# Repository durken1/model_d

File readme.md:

# Model D

## Note: I got this working using a fork of QMK for XWhatsit by deskthority user pandrew. There is probably room for improvement in the PCB - the current version is basically a working prototype, so use this at your own peril. No guarantees :)

40% ortho keyboard using a capacitive pcb and Model F switches.

The ground plate is important to avoid interference and is to be placed beneath the main pcb.

## Case
I have included the STLs (cut to be printable on "normal" sized printers, I used an Ender 3 V2) for my case as well as the step file, so it should be easy to make adjustments to fit your need. 
I used M3 inserts and screws for attaching stuff (all the 4mm round holes).

The PCBs slide into the plate that is then attached to the main case using the mounting bracket. The plate is designed with 0.8 mm PCBs in mind (1.6 mm total for main + ground pcb).

I think most of the assembly is pretty straight forward, so I won't make a guide unless there is demand for one. Feel free to contact me with any questions though.

For my build I used a TH-xwhatsit and a short USB C panel mount extension cable.

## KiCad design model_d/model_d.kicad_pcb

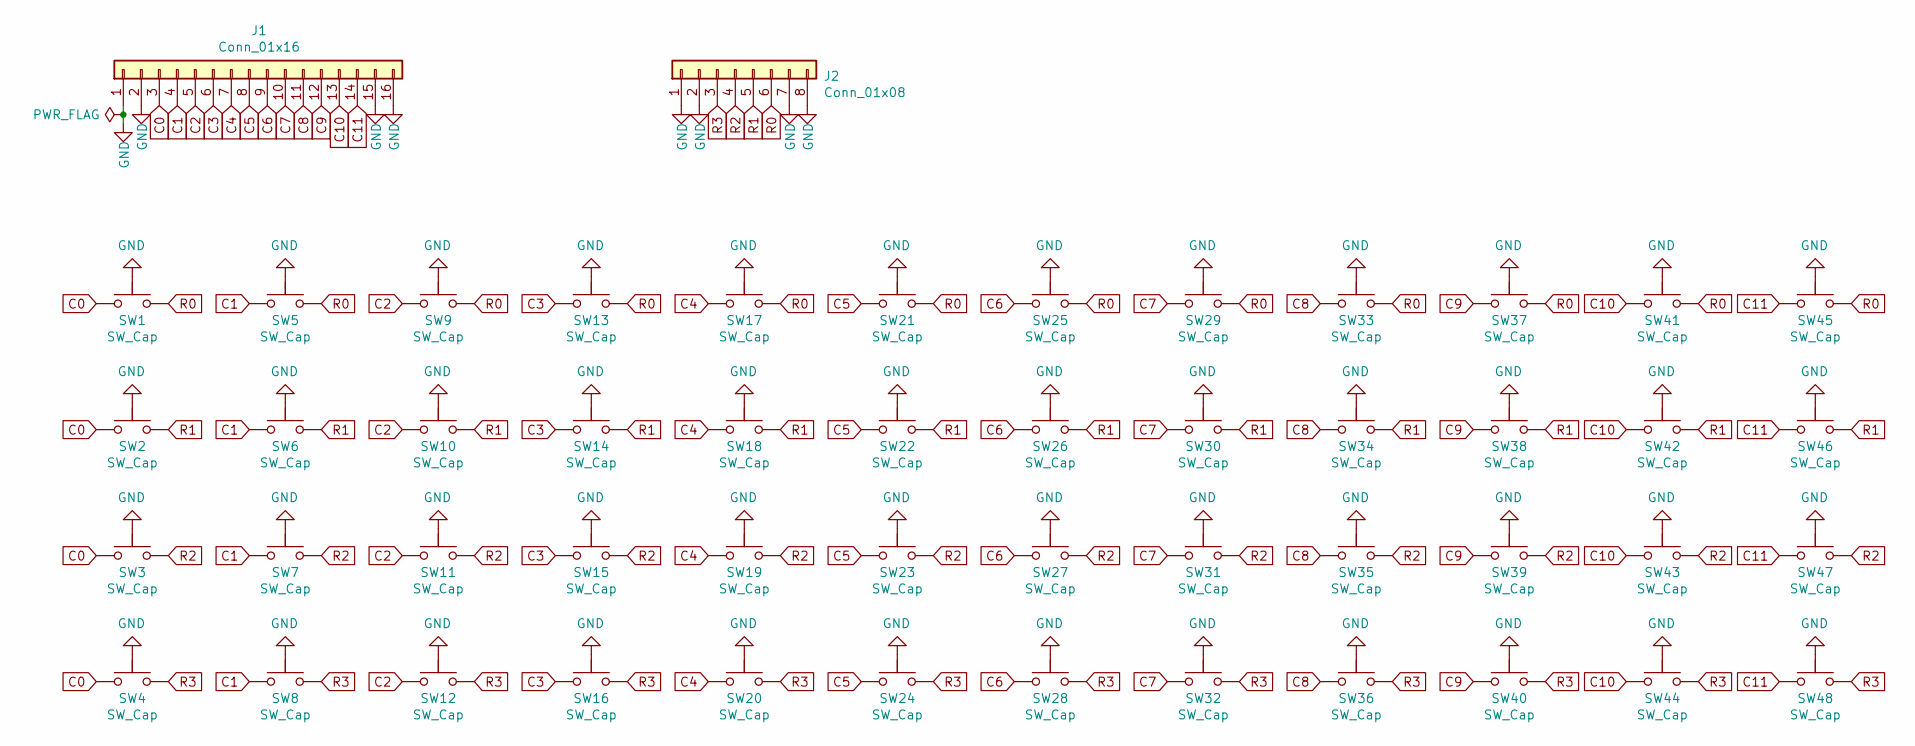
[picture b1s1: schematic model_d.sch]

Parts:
J1: Conn_01x16; PinHeader_1x16_P2.54mm_Vertical
J2: Conn_01x08; PinHeader_1x08_P2.54mm_Vertical
SW1, SW2, SW3, SW4, SW5, SW6, SW7, SW8, SW9, SW10, SW11, SW12, SW13, SW14, SW15, SW16, SW17, SW18, SW19, SW20, SW21, SW22, SW23, SW24, SW25, SW26, SW27, SW28, SW29, SW30, SW31, SW32, SW33, SW34, SW35, SW36, SW37, SW38, SW39, SW40, SW41, SW42, SW43, SW44, SW45, SW46, SW47, SW48: SW_Cap; capswitch2

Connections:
C0: J1.3, SW1.DRIVE, SW2.DRIVE, SW3.DRIVE, SW4.DRIVE; also elsewhere on the board
C1: J1.4, SW5.DRIVE, SW6.DRIVE, SW7.DRIVE, SW8.DRIVE; also elsewhere on the board
C2: J1.5, SW9.DRIVE, SW10.DRIVE, SW11.DRIVE, SW12.DRIVE; also elsewhere on the board
C3: J1.6, SW13.DRIVE, SW14.DRIVE, SW15.DRIVE, SW16.DRIVE; also elsewhere on the board
C4: J1.7, SW17.DRIVE, SW18.DRIVE, SW19.DRIVE, SW20.DRIVE; also elsewhere on the board
C5: J1.8, SW21.DRIVE, SW22.DRIVE, SW23.DRIVE, SW24.DRIVE; also elsewhere on the board
C6: J1.9, SW25.DRIVE, SW26.DRIVE, SW27.DRIVE, SW28.DRIVE; also elsewhere on the board
C7: J1.10, SW29.DRIVE, SW30.DRIVE, SW31.DRIVE, SW32.DRIVE; also elsewhere on the board
C8: J1.11, SW33.DRIVE, SW34.DRIVE, SW35.DRIVE, SW36.DRIVE; also elsewhere on the board
C9: J1.12, SW37.DRIVE, SW38.DRIVE, SW39.DRIVE, SW40.DRIVE; also elsewhere on the board
C10: J1.13, SW41.DRIVE, SW42.DRIVE, SW43.DRIVE, SW44.DRIVE; also elsewhere on the board
C11: J1.14, SW45.DRIVE, SW46.DRIVE, SW47.DRIVE, SW48.DRIVE; also elsewhere on the board
GND: J1.1, J1.2, J1.15, J1.16, J2.1, J2.2, J2.7, J2.8, SW1.GND, SW2.GND, SW3.GND, SW4.GND, SW5.GND, SW6.GND, SW7.GND, SW8.GND, SW9.GND, SW10.GND, SW11.GND, SW12.GND, SW13.GND, SW14.GND, SW15.GND, SW16.GND, SW17.GND, SW18.GND, SW19.GND, SW20.GND, SW21.GND, SW22.GND, SW23.GND, SW24.GND, SW25.GND, SW26.GND, SW27.GND, SW28.GND, SW29.GND, SW30.GND, SW31.GND, SW32.GND, SW33.GND, SW34.GND, SW35.GND, SW36.GND, SW37.GND, SW38.GND, SW39.GND, SW40.GND, SW41.GND, SW42.GND, SW43.GND, SW44.GND, SW45.GND, SW46.GND, SW47.GND, SW48.GND; also elsewhere on the board
R0: J2.6, SW1.SENSE, SW5.SENSE, SW9.SENSE, SW13.SENSE, SW17.SENSE, SW21.SENSE, SW25.SENSE, SW29.SENSE, SW33.SENSE, SW37.SENSE, SW41.SENSE, SW45.SENSE; also elsewhere on the board
R1: J2.5, SW2.SENSE, SW6.SENSE, SW10.SENSE, SW14.SENSE, SW18.SENSE, SW22.SENSE, SW26.SENSE, SW30.SENSE, SW34.SENSE, SW38.SENSE, SW42.SENSE, SW46.SENSE; also elsewhere on the board
R2: J2.4, SW3.SENSE, SW7.SENSE, SW11.SENSE, SW15.SENSE, SW19.SENSE, SW23.SENSE, SW27.SENSE, SW31.SENSE, SW35.SENSE, SW39.SENSE, SW43.SENSE, SW47.SENSE; also elsewhere on the board
R3: J2.3, SW4.SENSE, SW8.SENSE, SW12.SENSE, SW16.SENSE, SW20.SENSE, SW24.SENSE, SW28.SENSE, SW32.SENSE, SW36.SENSE, SW40.SENSE, SW44.SENSE, SW48.SENSE; also elsewhere on the board

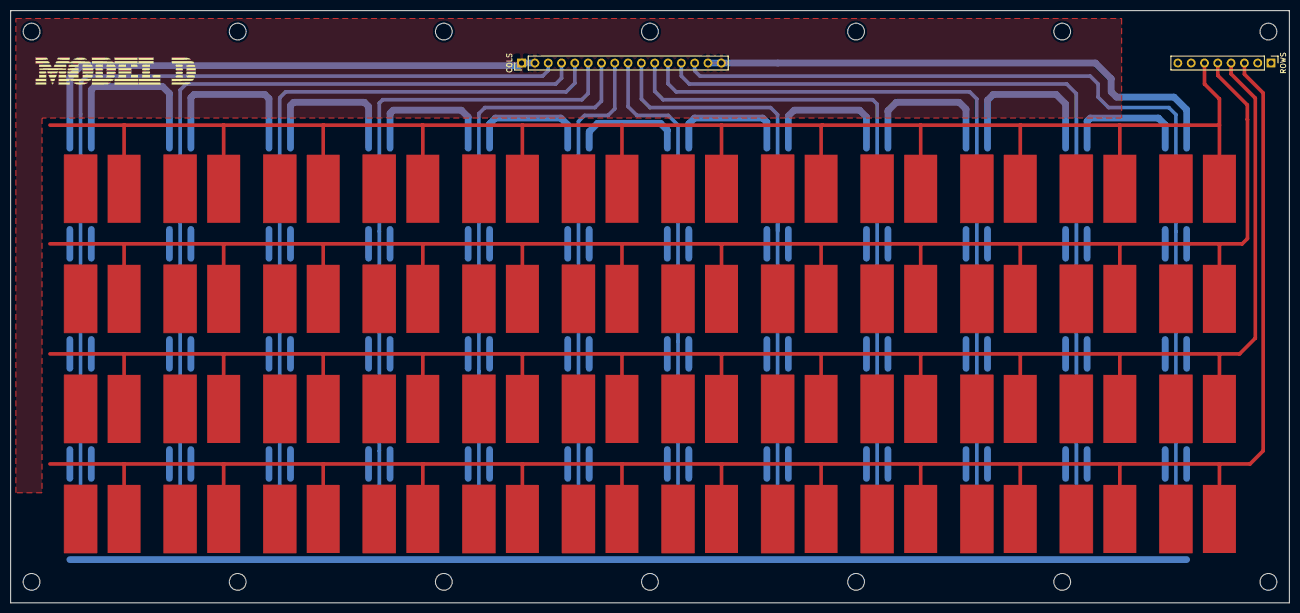
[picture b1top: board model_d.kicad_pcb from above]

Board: 2 copper layers, 244.0 x 113.0 mm, 50 parts (0 on the bottom side), 17 nets.

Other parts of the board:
COLS: Conn_01x16; PinHeader_1x16_P2.54mm_Vertical
ROWS: Conn_01x08; PinHeader_1x08_P2.54mm_Vertical

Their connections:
C0: COLS.3; also elsewhere on the board
C1: COLS.4; also elsewhere on the board
C2: COLS.5; also elsewhere on the board
C3: COLS.6; also elsewhere on the board
C4: COLS.7; also elsewhere on the board
C5: COLS.8; also elsewhere on the board
C6: COLS.9; also elsewhere on the board
C7: COLS.10; also elsewhere on the board
C8: COLS.11; also elsewhere on the board
C9: COLS.12; also elsewhere on the board
C10: COLS.13; also elsewhere on the board
C11: COLS.14; also elsewhere on the board
GND: COLS.1, COLS.2, COLS.15, COLS.16, ROWS.1, ROWS.2, ROWS.7, ROWS.8; also elsewhere on the board
R0: ROWS.6; also elsewhere on the board
R1: ROWS.5; also elsewhere on the board
R2: ROWS.4; also elsewhere on the board
R3: ROWS.3; also elsewhere on the board

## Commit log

2021-10-15 init commit
2021-10-15 add readme
2021-10-15 add .gitignore
2021-10-15 footprint done. place and route in progress
2021-10-19 complete place & route, add gnd plate
2021-11-15 add STLs, update readme, small cleanup
2021-12-29 add m3 mounting holes, increase size to 113x244
2022-01-16 update gerbers
2022-09-02 add case files
2022-09-02 add plate stl
2022-09-02 remove old proto plate
